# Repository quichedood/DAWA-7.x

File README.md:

# DAWA-7.x

Démo : https://youtu.be/l66AxoFr9uk

DAWA est un système de chronométrage et d'acquisition de données pour votre moto.
Il enregistre les données 10 fois par seconde dans un fichier CSV.

Specs/fonctionnalités :
- Ecran TFT tactile 4,3" couleur (resistif)
- Carte micro SD
- Antenne GPS externe
- Alimentation externe via batterie 12v
- Indicateur 8 leds paramétrable
- Position GPS (10Hz)
- Chronométrage circuit
- 2 entrées numériques (binaire)
- 2 entrées numériques (signal carré, fréquence)
- 8 entrées analogiques
- 6 capteurs de température infrarouge
- Module OBD (prise diagnostique)

Exemple de mesures :
- Vitesse (GPS ou basé sur une entrée numérique)
- Rapport de vitesse engagé (basé sur une entrée analogique)
- Régime moteur (basé sur une entrée numérique)
- Capteur de pression de frein (basé sur une entrée analogique)

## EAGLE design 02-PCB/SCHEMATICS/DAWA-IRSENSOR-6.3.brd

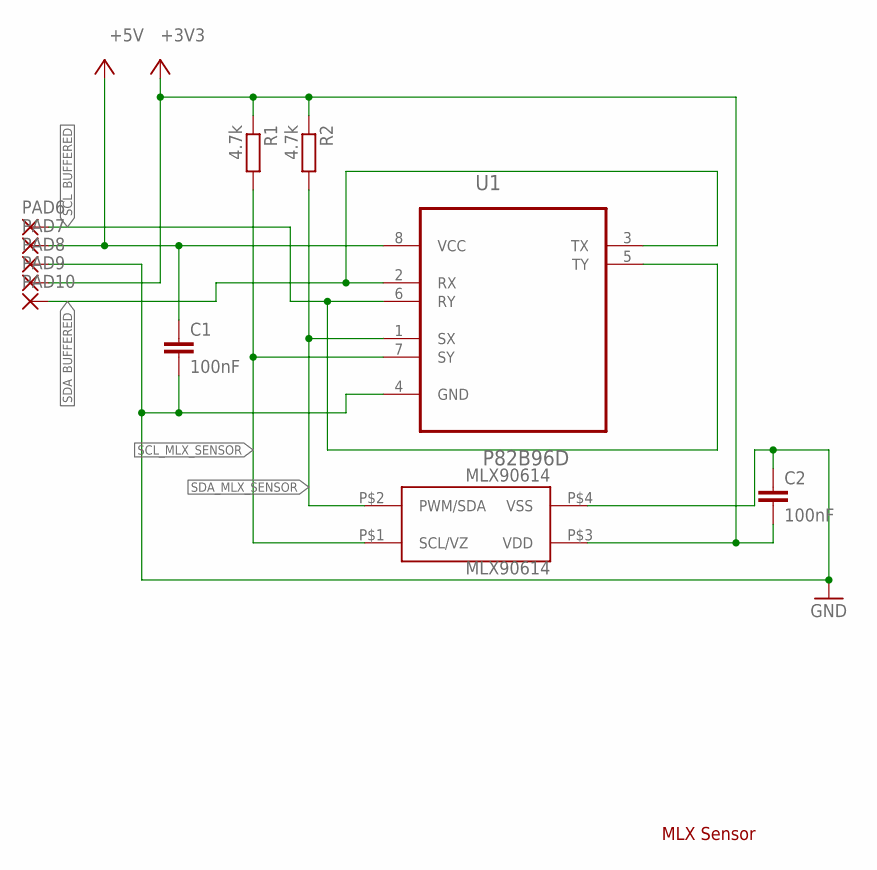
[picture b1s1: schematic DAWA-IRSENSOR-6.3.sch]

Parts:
C1, C2: 100nF; C0603
MLX90614: MLX90614; TO-39
PAD6, PAD7, PAD8, PAD9, PAD10: WIREPAD1,6/0,9; 1,6/0,9
R1, R2: 4.7k; R0603
U1: P82B96D; SOIC127P600X175-8N

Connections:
+3V3: C2.2, MLX90614.P$3 (VDD), PAD9.1, R1.1, R2.1
+5V: C1.1, PAD7.1, U1.8 (VCC)
GND: C1.2, C2.1, MLX90614.P$4 (VSS), PAD8.1, U1.4 (GND)
SCL_BUFFERED: PAD6.1, U1.5 (TY), U1.6 (RY)
SCL_MLX_SENSOR: MLX90614.P$1 (SCL/VZ), R1.2, U1.7 (SY)
SDA_BUFFERED: PAD10.1, U1.2 (RX), U1.3 (TX)
SDA_MLX_SENSOR: MLX90614.P$2 (PWM/SDA), R2.2, U1.1 (SX)

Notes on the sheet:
MLX Sensor

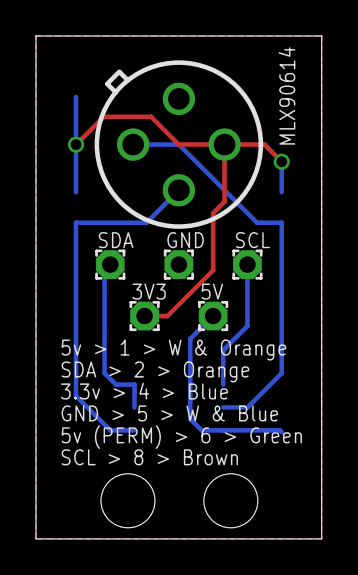
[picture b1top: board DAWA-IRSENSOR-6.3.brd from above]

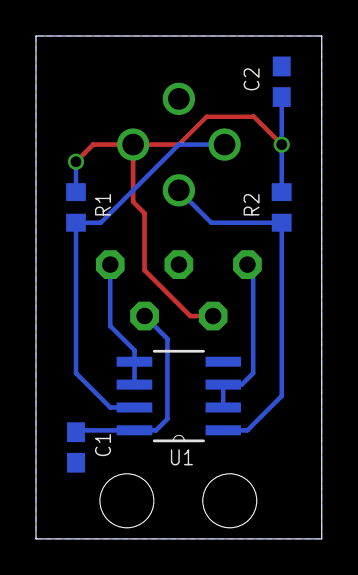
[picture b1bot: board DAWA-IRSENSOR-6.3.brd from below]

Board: 2 copper layers, 15.9 x 27.9 mm, 11 parts (5 on the bottom side), 7 nets.

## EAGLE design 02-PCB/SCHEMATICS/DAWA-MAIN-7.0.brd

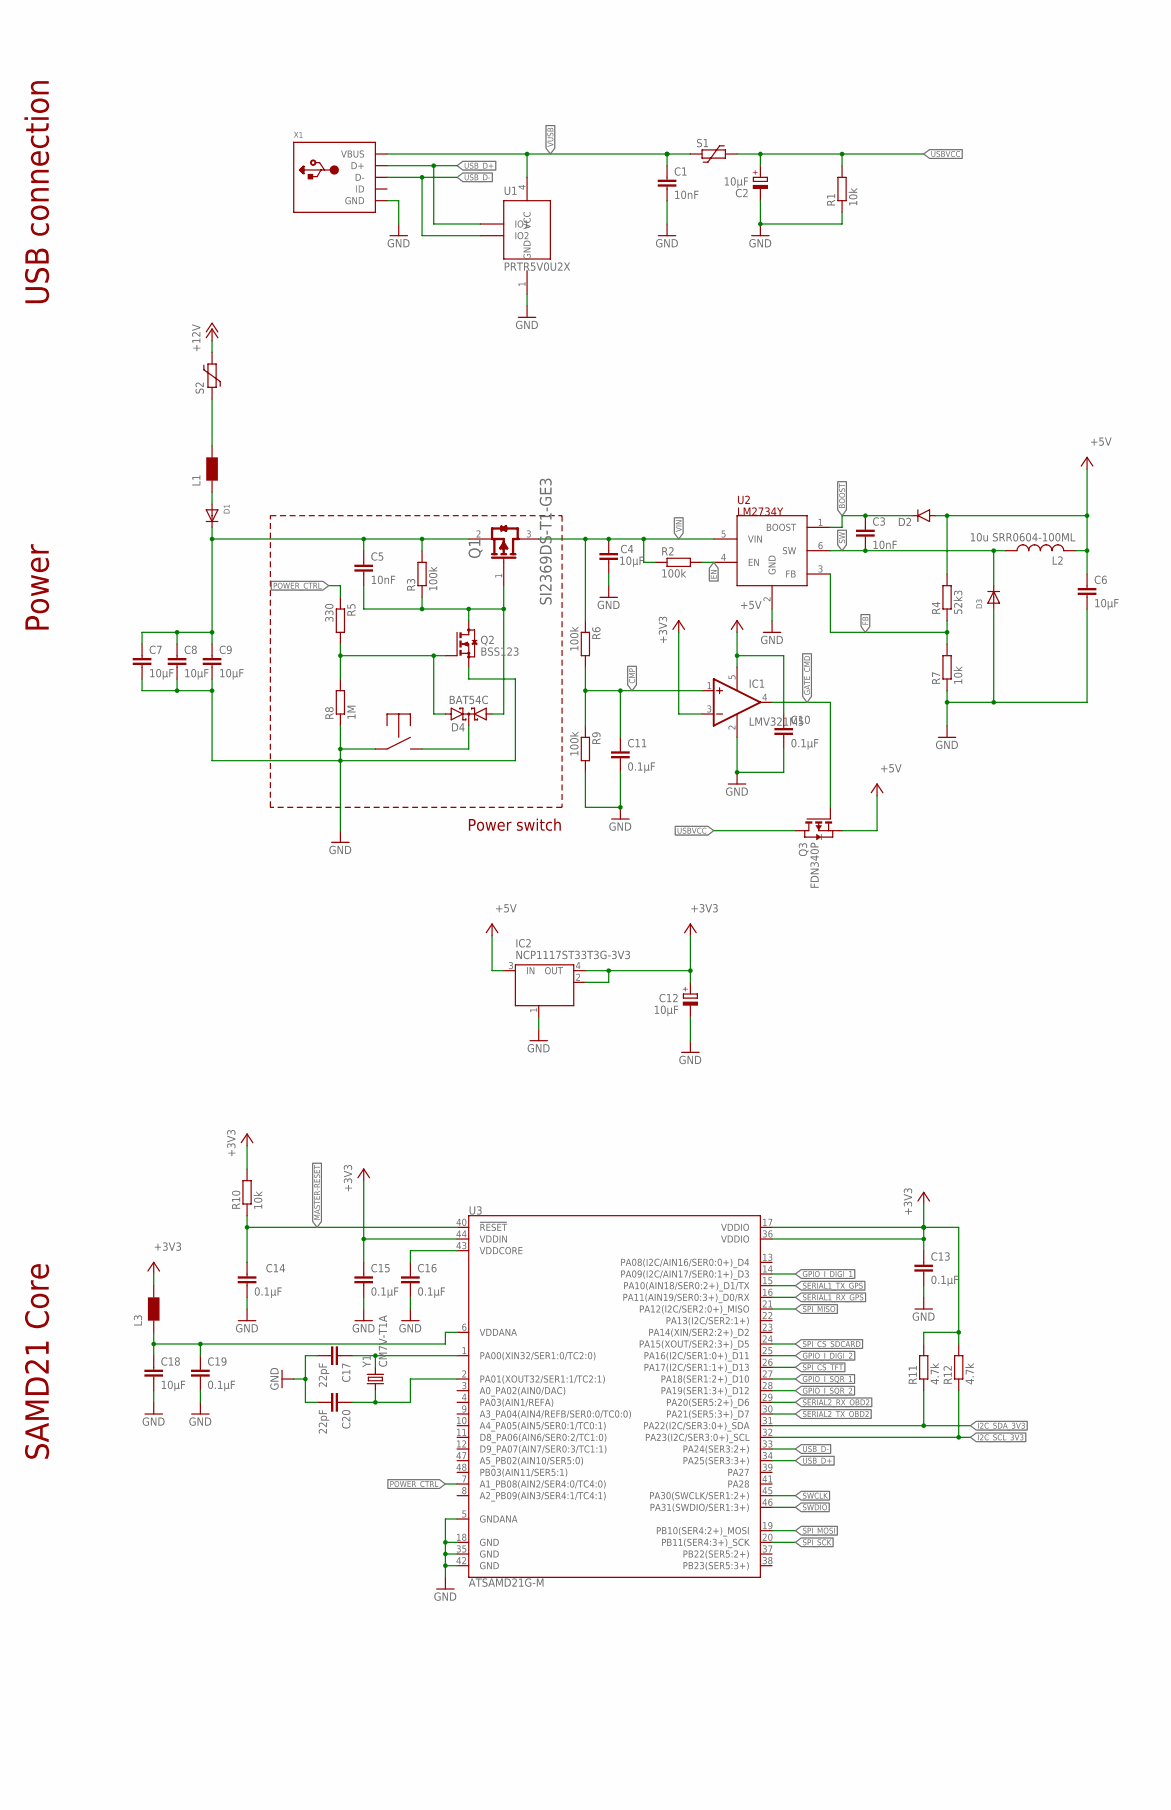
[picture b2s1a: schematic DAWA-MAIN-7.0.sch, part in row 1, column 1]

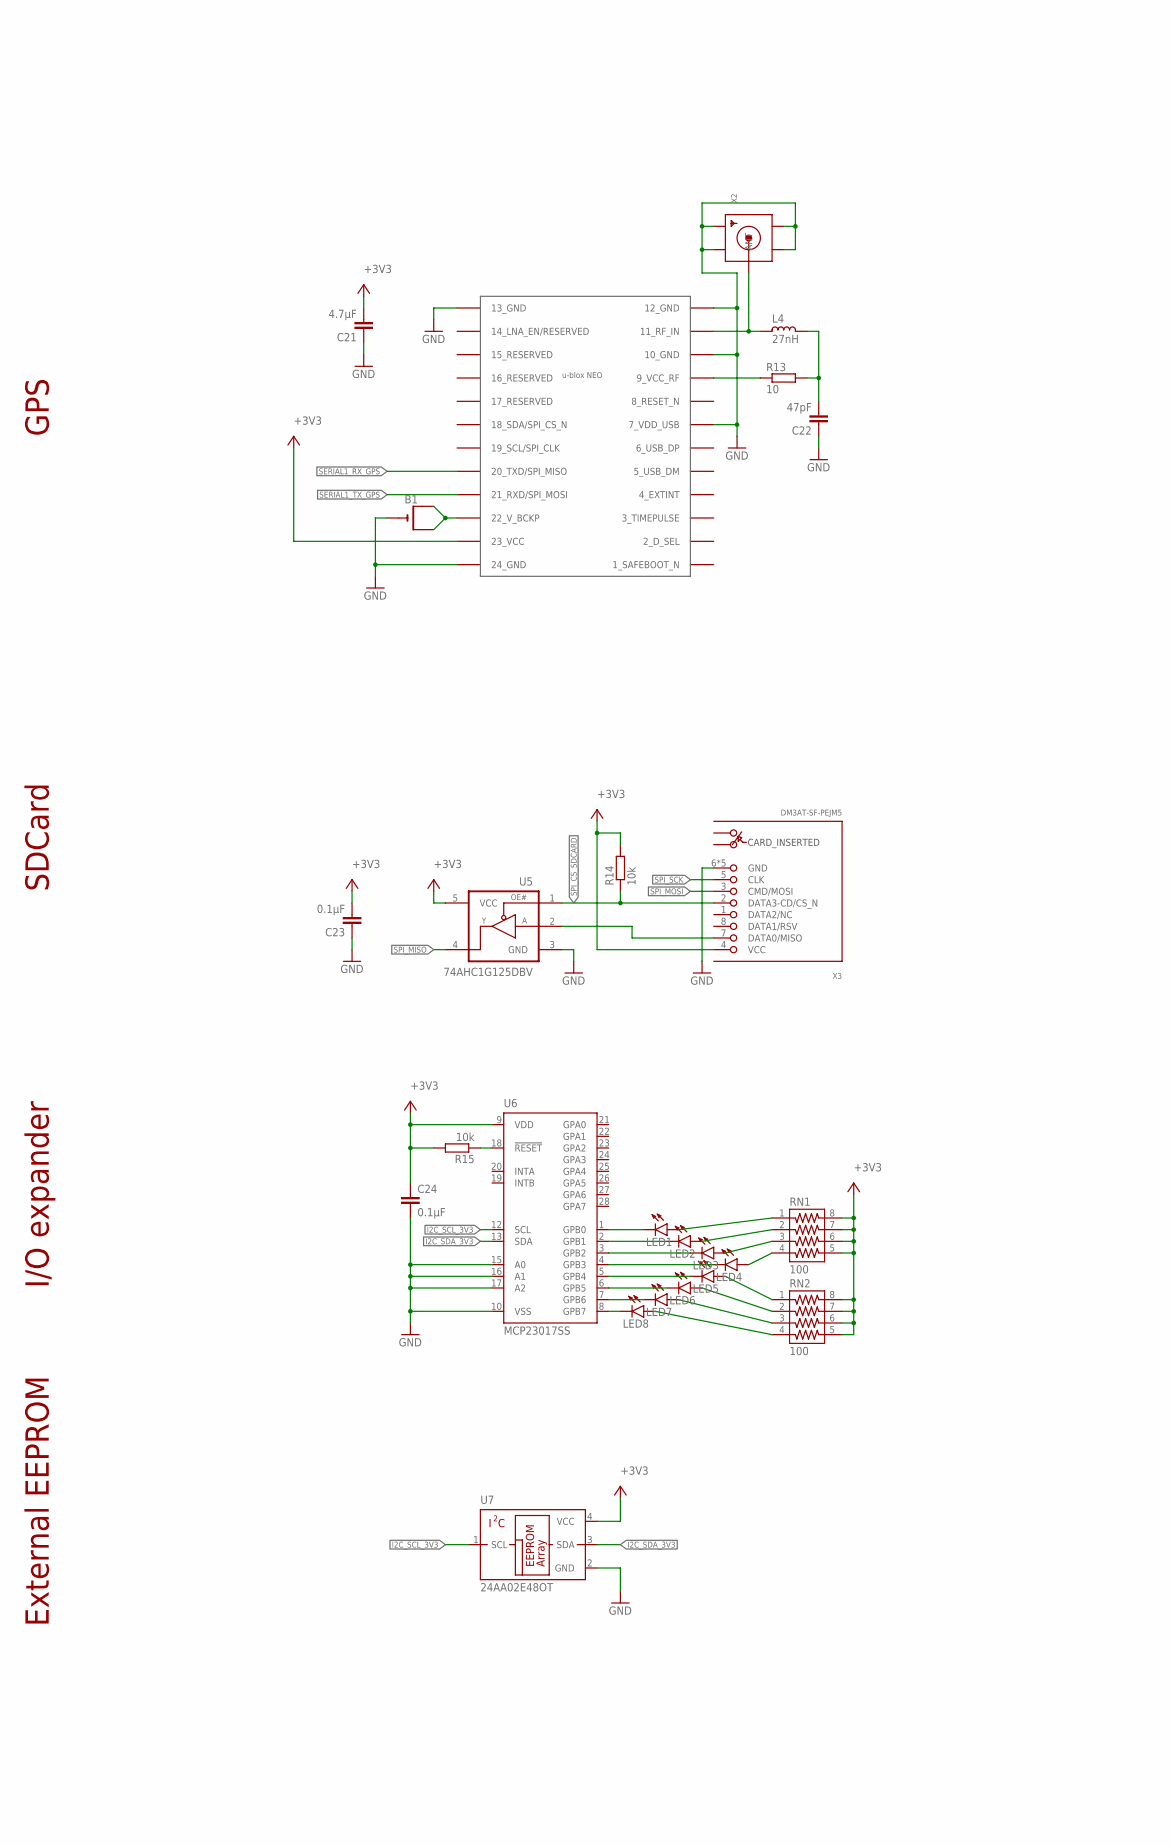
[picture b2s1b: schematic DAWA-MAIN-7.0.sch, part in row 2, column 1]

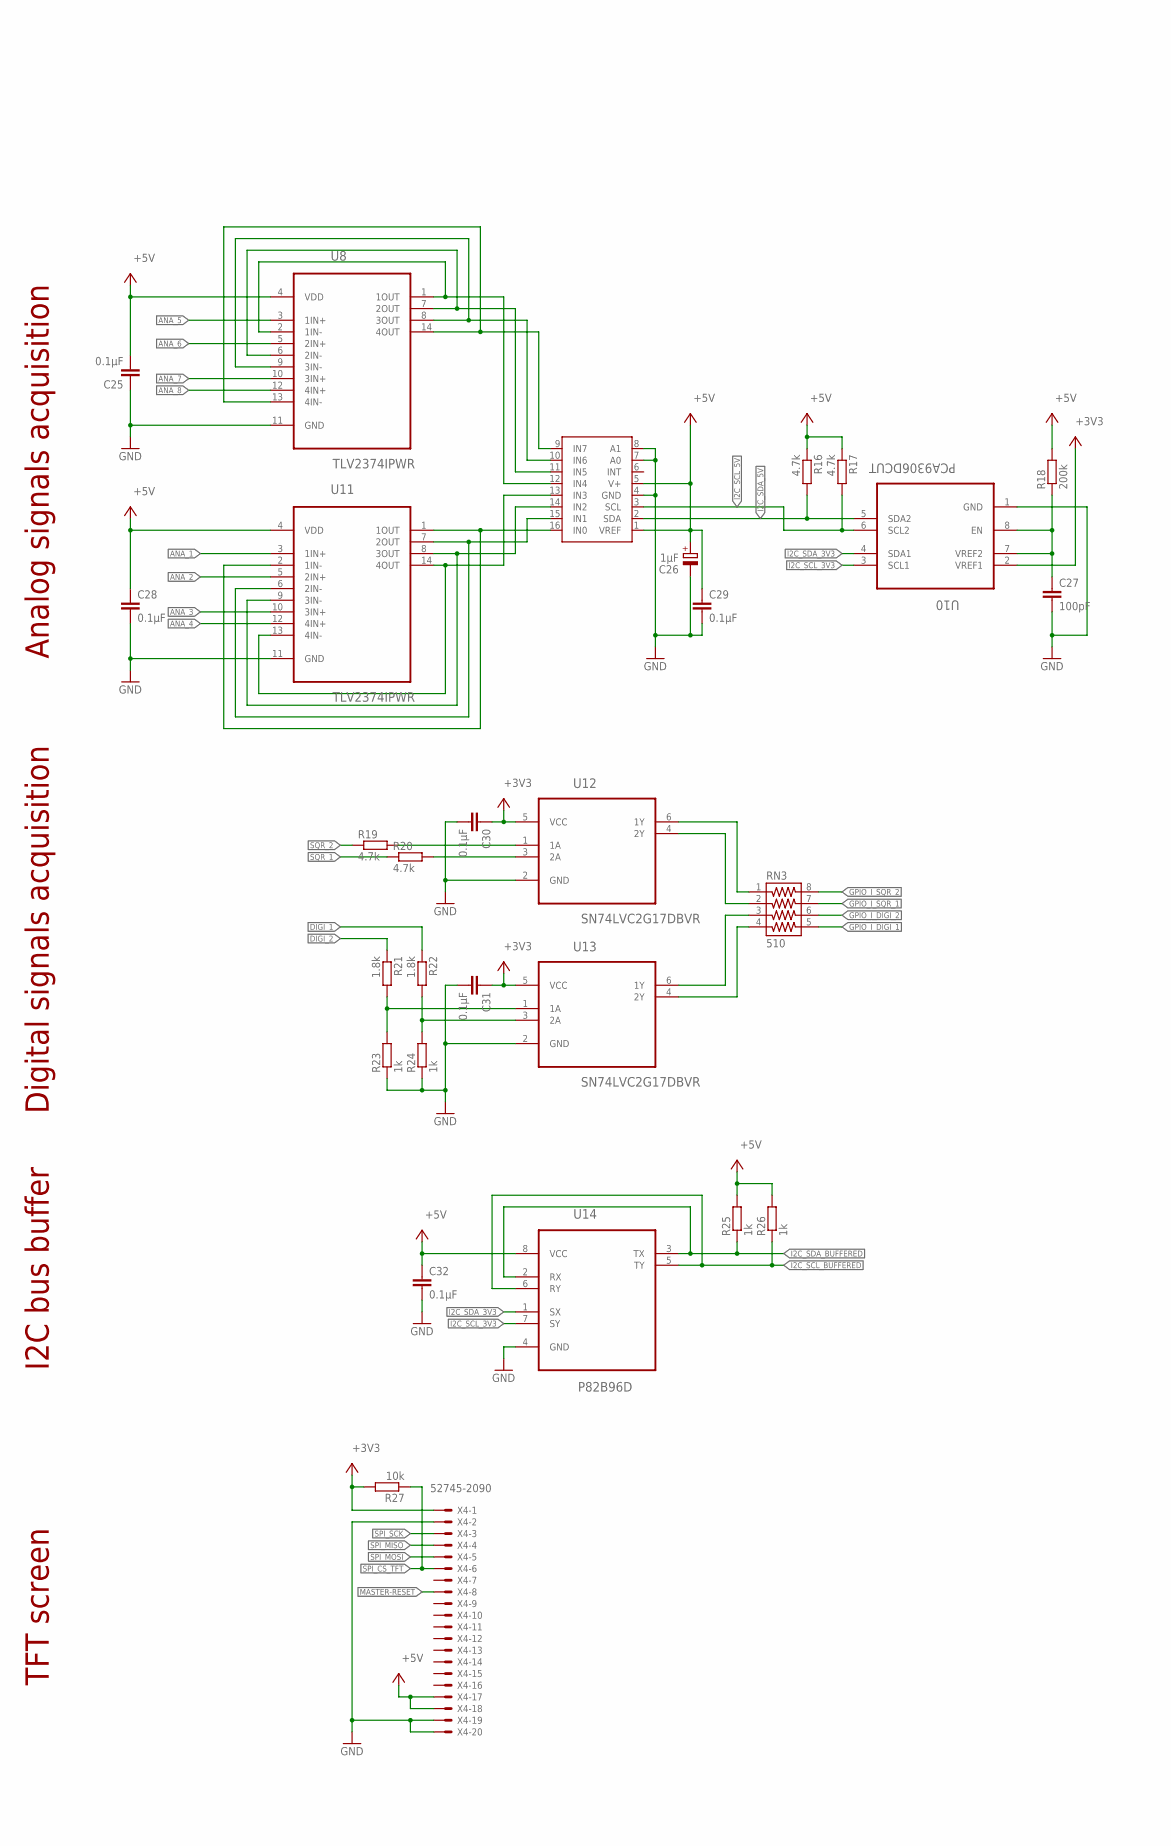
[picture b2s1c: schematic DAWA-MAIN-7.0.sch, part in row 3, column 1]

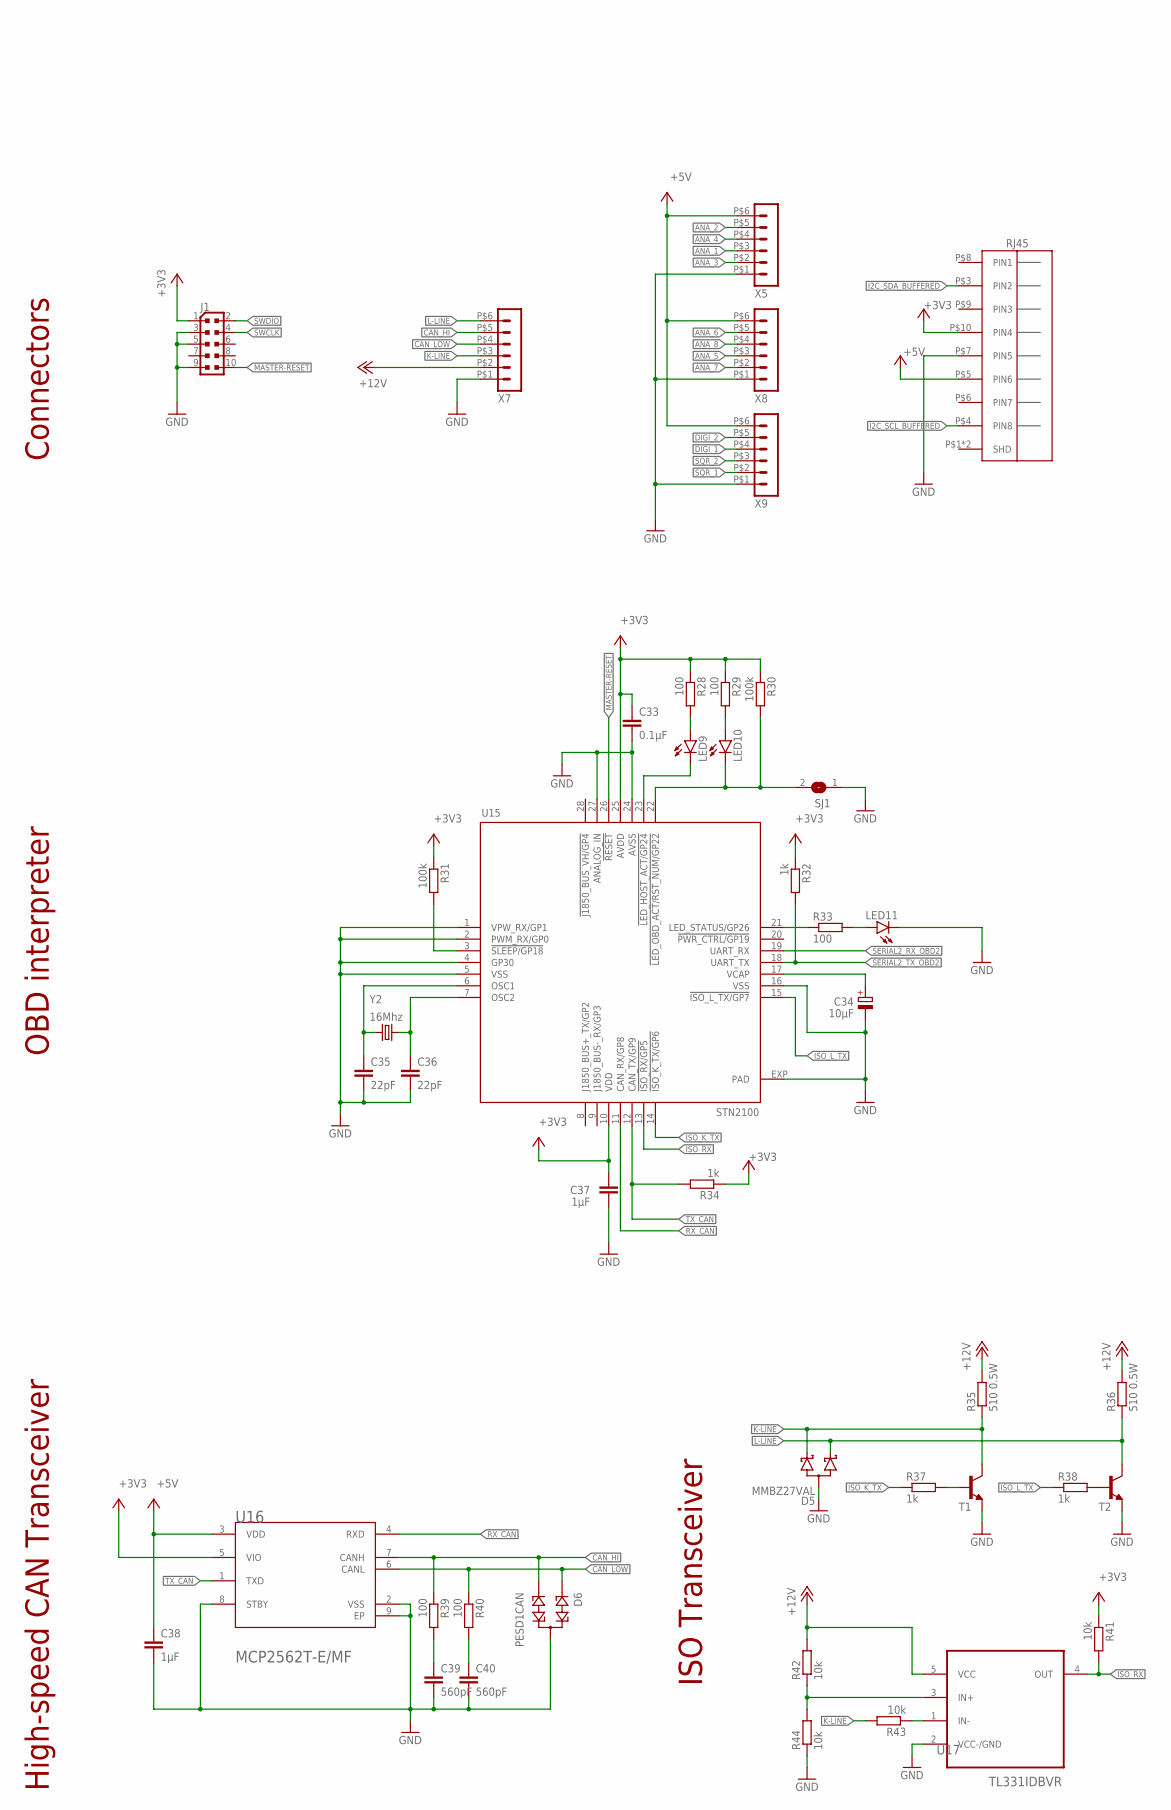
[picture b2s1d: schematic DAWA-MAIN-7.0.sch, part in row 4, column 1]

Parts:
B1: CR1220SMT; CR1220-SMD
C1, C3, C5: 10nF; C0603
C2, C12, C34: 10µF; SMC_B
C4, C6, C7, C8, C9, C18: 10µF; C0805
C10, C11, C13, C14, C15, C16, C19, C23, C24, C25, C28, C29, C30, C31, C32, C33: 0.1µF; C0603
C17, C20, C35, C36: 22pF; C0603
C21: 4.7µF; C0603
C22: 47pF; C0603
C26: 1µF; SMC_B
C27: 100pF; C0603
C37, C38: 1µF; C0603
C39, C40: 560pF; C0603
D1, D3: MBR120_SOD-123FL; SOD-123FL
D2: CD1206-S01575MINIMELF; MINIMELF
D4: BAT54C; SOT23
D5: MMBZ27VAL; SOT23
D6: PESD1CAN; SOT23
IC1: LMV321M5; SOT23-5
IC2: NCP1117ST33T3G-3V3; SOT223
J1: PINHD-2X5PASSO127; ARDUINO_WIFI_SHIELD_V018_TG_PINHEAD_2X05_127
L1, L3: MH2029-300Y_0805; WUERTH-ELEKTRONIK_0805
L2: 10u SRR0604-100ML; SRR0604
L4: 27nH; RC-MASTER-SMD_L0603
LED1, LED2, LED3, LED4, LED5, LED6, LED7, LED8, LED9, LED10, LED11: LEDCHIPLED_0603; CHIPLED_0603
Q1: SI2369DS-T1-GE3VISHAY_SI2369DS-T1-GE3_0_0; VISHAY_SI2369DS-T1-GE3_0
Q2: BSS123; SOT23
Q3: FDN340P; SOT-23
R1, R7, R10, R14, R15, R27, R41, R42, R43, R44: 10k; R0603
R2, R3, R6, R9, R30, R31: 100k; R0603
R4: 52k3; R0603
R5: 330; R0603
R8: 1M; R0603
R11, R12, R16, R17, R19, R20: 4.7k; R0603
R13: 10; R0603
R18: 200k; R0603
R21, R22: 1.8k; R0603
R23, R24, R25, R26, R32, R34, R37, R38: 1k; R0603
R28, R29, R33, R39, R40: 100; R0603
R35, R36: 510 0.5W; R0603
RN1, RN2: 100; 742-8NS
RN3: 510; 742-8NS
S1: MF-NSMF050-1206; MF-1206
S2: MF-MSMF050-1812; MF-1812
S3: SKPMAPE10
SJ1: SJ
T1, T2: MMBT2222ALT1-NPN-SOT23-BEC; SOT23-BEC
U1: PRTR5V0U2X; SOT-143B
U2: LM2734Y; SOT23-6
U3: ATSAMD21G-M; QFN-48
U4: NEO-M8
U5: 74AHC1G125DBV; SOT23-5
U6: MCP23017SS; SSOP28
U7: 24AA02E48OT; SOT23-5
U8, U11: TLV2374IPWR; SOP65P640X120-14N
U9: ADC128D818; ADC12_SD
U10: PCA9306DCUT; SOP50P310X90-8N
U12, U13: SN74LVC2G17DBVR; SOT95P280X145-6N
U14: P82B96D; SOIC127P600X175-8N
U15: STN2100; QFN-28-S
U16: MCP2562T-E-MFMICROCHIP_MCP2562T-E-MF_0_2; MICROCHIP_MCP2562T-E-MF_2
U17: TL331IDBVR; SOT95P280X145-5N
X1: USB; USB-MINIB-DAWA
X2: SMACONNECTOR_EDGE; SMA_EDGELAUNCH
X3: DM3AT-SF-PEJM5
X4: 52745-2090
X5, X7, X8, X9: HEADER_POS6_43045-0600; 43045-0600
X6: RJ45
Y1: CM7V-T1A; KANFLO_OSCILLATOR_SMD
Y2: 16Mhz; 3.2X2.5_KX-7

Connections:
+3V3: C12.+, C13.1, C15.1, C21.2, C23.2, C24.1, C30.1, C31.1, C33.1, C37.1, IC1.3 (-IN), IC2.2 (OUT), IC2.4 (OUT), J1.1, L3.2, R10.2, R11.2, R12.2, R14.2, R15.2, R27.2, R28.1, R29.1, R30.1, R31.1, R32.1, R34.1, R41.1, RN1.5, RN1.6, RN1.7, RN1.8, RN2.5, RN2.6, RN2.7, RN2.8, U3.17 (VDDIO), U3.36 (VDDIO), U3.44 (VDDIN), U4.23 (23_VCC), U5.5 (VCC), U6.9 (VDD), U7.4 (VCC), U10.2 (VREF1), U12.5 (VCC), U13.5 (VCC), U15.10 (VDD), U15.25 (AVDD), U16.5 (VIO), X3.4 (VCC), X4.1, X6.P$10 (PIN4)
+5V: C6.1, C10.1, C25.2, C26.+, C28.1, C29.1, C32.1, C38.1, D2.A, IC1.5 (V+), IC2.3 (IN), L2.P$2 (2), Q3.2 (S), R4.2, R16.1, R17.1, R18.2, R25.2, R26.2, U8.4 (VDD), U9.1 (VREF), U9.5 (V+), U11.4 (VDD), U14.8 (VCC), U16.3 (VDD), X4.17, X4.18, X5.P$6 (6), X6.P$5 (PIN6), X8.P$6 (6), X9.P$6 (6)
+12V: R35.2, R36.2, R42.2, S2.1, U17.5 (VCC), X7.P$2 (2)
ANA_1: U11.3 (1IN+), X5.P$3 (3)
ANA_2: U11.5 (2IN+), X5.P$5 (5)
ANA_3: U11.10 (3IN+), X5.P$2 (2)
ANA_4: U11.12 (4IN+), X5.P$4 (4)
ANA_5: U8.3 (1IN+), X8.P$3 (3)
ANA_6: U8.5 (2IN+), X8.P$5 (5)
ANA_7: U8.10 (3IN+), X8.P$2 (2)
ANA_8: U8.12 (4IN+), X8.P$4 (4)
BOOST: C3.1, D2.C, U2.1 (BOOST)
CAN_HI: D6.2, R39.1, U16.7 (CANH), X7.P$5 (5)
CAN_LOW: D6.1, R40.1, U16.6 (CANL), X7.P$4 (4)
CMP: C11.1, IC1.1 (+IN), R6.2, R9.1
DIGI_1: R22.1, X9.P$4 (4)
DIGI_2: R21.1, X9.P$5 (5)
EN: R2.2, U2.4 (EN)
FB: R4.1, R7.2, U2.3 (FB)
GATE_CMD: IC1.4 (OUT), Q3.3 (G)
GND: B1.-, C1.2, C2.-, C4.2, C6.2, C7.2, C8.2, C9.2, C10.2, C11.2, C12.-, C13.2, C14.2, C15.2, C16.2, C17.2, C18.2, C19.2, C20.2, C21.1, C22.1, C23.1, C24.2, C25.1, C26.-, C27.2, C28.2, C29.2, C30.2, C31.2, C32.2, C33.2, C34.-, C35.2, C36.2, C37.2, C38.2, C39.2, C40.2, D3.A, D5.3 (A), D6.3, IC1.2 (V-), IC2.1 (GND/ADJ), J1.3, J1.5, J1.9, LED11.C, Q2.2 (S), R1.1, R7.1, R8.1, R9.2, R23.1, R24.1, R44.1, S3.P$1, SJ1.1, T1.E, T2.E, U1.1 (GND), U2.2 (GND), U3.5 (GNDANA), U3.18 (GND), U3.35 (GND), U3.42 (GND), U4.7 (7_VDD_USB), U4.10 (10_GND), U4.12 (12_GND), U4.13 (13_GND), U4.24 (24_GND), U5.3 (GND), U6.10 (VSS), U6.15 (A0), U6.16 (A1), U6.17 (A2), U7.2 (GND), U8.11 (GND), U9.4 (GND), U9.7 (A0), U9.8 (A1), U10.1 (GND), U11.11 (GND), U12.2 (GND), U13.2 (GND), U14.4 (GND), U15.1 (VPW_RX/GP1), U15.2 (PWM_RX/GP0), U15.4 (GP30), U15.5 (VSS), U15.16 (VSS), U15.24 (AVSS), U15.27 (ANALOG_IN), U15.EXP (PAD), U16.2 (VSS), U16.8 (STBY), U16.9 (EP), U17.2 (VCC-/GND), X1.GND, X1.GND1 (GND), X1.GND2 (GND), X2.GND@1 (GND4), X2.GND@2 (GND3), X2.GND@3 (GND2), X2.GND@4 (GND1), X3.6 (GND), X3.MOUNT0 (GND), X3.MOUNT1 (GND), X3.MOUNT2 (GND), X3.MOUNT3 (GND), X4.2, X4.19, X4.20, X5.P$1 (1), X6.P$7 (PIN5), X7.P$1 (1), X8.P$1 (1), X9.P$1 (1)
GPIO_I_DIGI_1: RN3.5, U3.14 (PA09(I2C/AIN17/SER0:1+)_D3)
GPIO_I_DIGI_2: RN3.6, U3.25 (PA16(I2C/SER1:0+)_D11)
GPIO_I_SQR_1: RN3.7, U3.27 (PA18(SER1:2+)_D10)
GPIO_I_SQR_2: RN3.8, U3.28 (PA19(SER1:3+)_D12)
I2C_SCL_3V3: R12.1, U3.32 (PA23(I2C/SER3:0+)_SCL), U6.12 (SCL), U7.1 (SCL), U10.3 (SCL1), U14.7 (SY)
I2C_SCL_5V: R17.2, U9.3 (SCL), U10.6 (SCL2)
I2C_SCL_BUFFERED: R26.1, U14.5 (TY), U14.6 (RY), X6.P$4 (PIN8)
I2C_SDA_3V3: R11.1, U3.31 (PA22(I2C/SER3:0+)_SDA), U6.13 (SDA), U7.3 (SDA), U10.4 (SDA1), U14.1 (SX)
I2C_SDA_5V: R16.2, U9.2 (SDA), U10.5 (SDA2)
I2C_SDA_BUFFERED: R25.1, U14.2 (RX), U14.3 (TX), X6.P$3 (PIN2)
ISO_K_TX: R37.1, U15.14 (!ISO_K_TX/GP6)
ISO_L_TX: R38.1, U15.15 (!ISO_L_TX/GP7)
ISO_RX: R41.2, U15.13 (!ISO_RX/GP5), U17.4 (OUT)
K-LINE: D5.2 (C2), R35.1, R43.2, T1.C, X7.P$3 (3)
L-LINE: D5.1 (C1), R36.1, T2.C, X7.P$6 (6)
MASTER-RESET: C14.1, J1.10, R10.1, U3.40 (!RESET!), U15.26 (!RESET), X4.8
unnamed: C16.1, U3.43 (VDDCORE)
unnamed: C17.1, U3.1 (PA00(XIN32/SER1:0/TC2:0)), Y1.2
unnamed: C20.1, U3.2 (PA01(XOUT32/SER1:1/TC2:1)), Y1.1
unnamed: LED1.C, U6.1 (GPB0)
unnamed: B1.+$1 (+), B1.+$2 (+1), U4.22 (22_V_BCKP)
unnamed: LED2.C, U6.2 (GPB1)
unnamed: C5.1, C7.1, C8.1, C9.1, D1.C, Q1.2 (S), R3.2
unnamed: LED1.A, RN1.1
unnamed: D1.A, L1.1
unnamed: C22.2, L4.1, R13.2
unnamed: LED2.A, RN1.2
unnamed: U5.2 (A), X3.7 (DATA0/MISO)
unnamed: LED5.C, U6.5 (GPB4)
unnamed: C27.1, R18.1, U10.7 (VREF2), U10.8 (EN)
unnamed: LED6.C, U6.6 (GPB5)
unnamed: LED7.C, U6.7 (GPB6)
unnamed: LED8.C, U6.8 (GPB7)
unnamed: R13.1, U4.9 (9_VCC_RF)
unnamed: L4.2, U4.11 (11_RF_IN), X2.P (ANT)
unnamed: LED3.A, RN1.3
unnamed: LED3.C, U6.3 (GPB2)
unnamed: LED4.C, U6.4 (GPB3)
unnamed: LED4.A, RN1.4
unnamed: LED5.A, RN2.1
unnamed: LED6.A, RN2.2
unnamed: U9.16 (IN0), U11.1 (1OUT), U11.2 (1IN-)
unnamed: U9.15 (IN1), U11.6 (2IN-), U11.7 (2OUT)
unnamed: LED7.A, RN2.3
unnamed: LED8.A, RN2.4
unnamed: U9.14 (IN2), U11.8 (3OUT), U11.9 (3IN-)
unnamed: LED10.C, R30.2, SJ1.2, U15.22 (!LED_OBD_ACT/RST_NUM/GP22)
unnamed: R37.2, T1.B
unnamed: R15.1, U6.18 (!RESET)
unnamed: U9.13 (IN3), U11.13 (4IN-), U11.14 (4OUT)
unnamed: RN3.1, U12.6 (1Y)
unnamed: L1.2, S2.2
unnamed: U8.8 (3OUT), U8.9 (3IN-), U9.10 (IN6)
unnamed: U8.6 (2IN-), U8.7 (2OUT), U9.11 (IN5)
unnamed: U8.1 (1OUT), U8.2 (1IN-), U9.12 (IN4)
unnamed: R19.2, U12.1 (1A)
unnamed: R20.2, U12.3 (2A)
unnamed: R22.2, R24.2, U13.3 (2A)
unnamed: R21.2, R23.2, U13.1 (1A)
unnamed: RN3.3, U13.6 (1Y)
unnamed: RN3.4, U13.4 (2Y)
unnamed: C5.2, D4.1 (A1), Q1.1 (G), Q2.3 (D), R3.1
unnamed: D4.3 (CC), S3.P$2
unnamed: RN3.2, U12.4 (2Y)
unnamed: D4.2 (A2), Q2.1 (G), R5.2, R8.2
unnamed: U8.13 (4IN-), U8.14 (4OUT), U9.9 (IN7)
unnamed: R38.2, T2.B
unnamed: R42.1, R44.2, U17.3 (IN+)
unnamed: R43.1, U17.1 (IN-)
unnamed: R31.2, U15.3 (!SLEEP/GP18)
unnamed: C35.1, U15.6 (OSC1), Y2.1
unnamed: C36.1, U15.7 (OSC2), Y2.3 (2)
unnamed: LED9.A, R28.2
unnamed: C34.+, U15.17 (VCAP)
unnamed: R33.1, U15.21 (LED_STATUS/GP26)
unnamed: LED11.A, R33.2
unnamed: LED10.A, R29.2
unnamed: LED9.C, U15.23 (!LED_HOST_ACT/GP24)
unnamed: C39.1, R39.2
unnamed: C40.1, R40.2
POWER_CTRL: R5.1, U3.7 (A1_PB08(AIN2/SER4:0/TC4:0))
RX_CAN: U15.11 (CAN_RX/GP8), U16.4 (RXD)
SERIAL1_RX_GPS: U3.16 (PA11(AIN19/SER0:3+)_D0/RX), U4.20 (20_TXD/SPI_MISO)
SERIAL1_TX_GPS: U3.15 (PA10(AIN18/SER0:2+)_D1/TX), U4.21 (21_RXD/SPI_MOSI)
SERIAL2_RX_OBD2: U3.29 (PA20(SER5:2+)_D6), U15.19 (UART_RX)
SERIAL2_TX_OBD2: R32.2, U3.30 (PA21(SER5:3+)_D7), U15.18 (UART_TX)
SPI_CS_SDCARD: R14.1, U3.24 (PA15(XOUT/SER2:3+)_D5), U5.1 (OE#), X3.2 (DATA3-CD/CS_N)
SPI_CS_TFT: R27.1, U3.26 (PA17(I2C/SER1:1+)_D13), X4.6
SPI_MISO: U3.21 (PA12(I2C/SER2:0+)_MISO), U5.4 (Y), X4.4
SPI_MOSI: U3.19 (PB10(SER4:2+)_MOSI), X3.3 (CMD/MOSI), X4.5
SPI_SCK: U3.20 (PB11(SER4:3+)_SCK), X3.5 (CLK), X4.3
SQR_1: R20.1, X9.P$2 (2)
SQR_2: R19.1, X9.P$3 (3)
SW: C3.2, D3.C, L2.P$1 (1), U2.6 (SW)
SWCLK: J1.4, U3.45 (PA30(SWCLK/SER1:2+))
SWDIO: J1.2, U3.46 (PA31(SWDIO/SER1:3+))
TX_CAN: R34.2, U15.12 (CAN_TX/GP9), U16.1 (TXD)
USBVCC: C2.+, Q3.1 (D), R1.2, S1.2
USB_D+: U1.2 (IO1), U3.34 (PA25(SER3:3+)), X1.D+
USB_D-: U1.3 (IO2), U3.33 (PA24(SER3:2+)), X1.D-
VDDANA: C18.1, C19.1, L3.1, U3.6 (VDDANA)
VIN: C4.1, Q1.3 (D), R2.1, R6.1, U2.5 (VIN)
VUSB: C1.1, S1.1, U1.4 (VCC), X1.VBUS

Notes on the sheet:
SAMD21 Core
Power
USB connection
GPS
SDCard
I/O expander
Analog signals acquisition
Digital signals acquisition
I2C bus buffer
External EEPROM
Connectors
OBD interpreter
High-speed CAN Transceiver
TFT screen
Power switch
ISO Transceiver

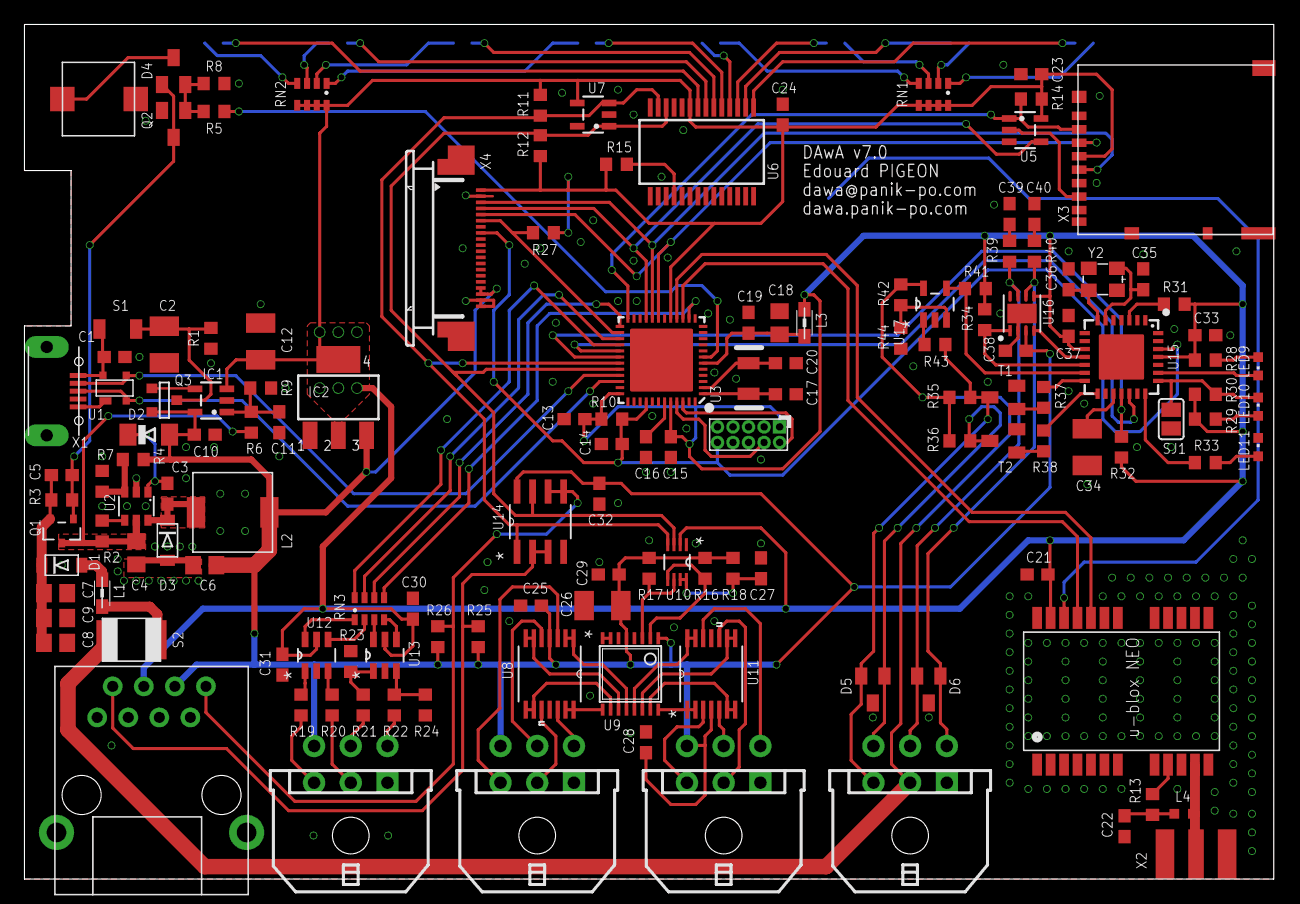
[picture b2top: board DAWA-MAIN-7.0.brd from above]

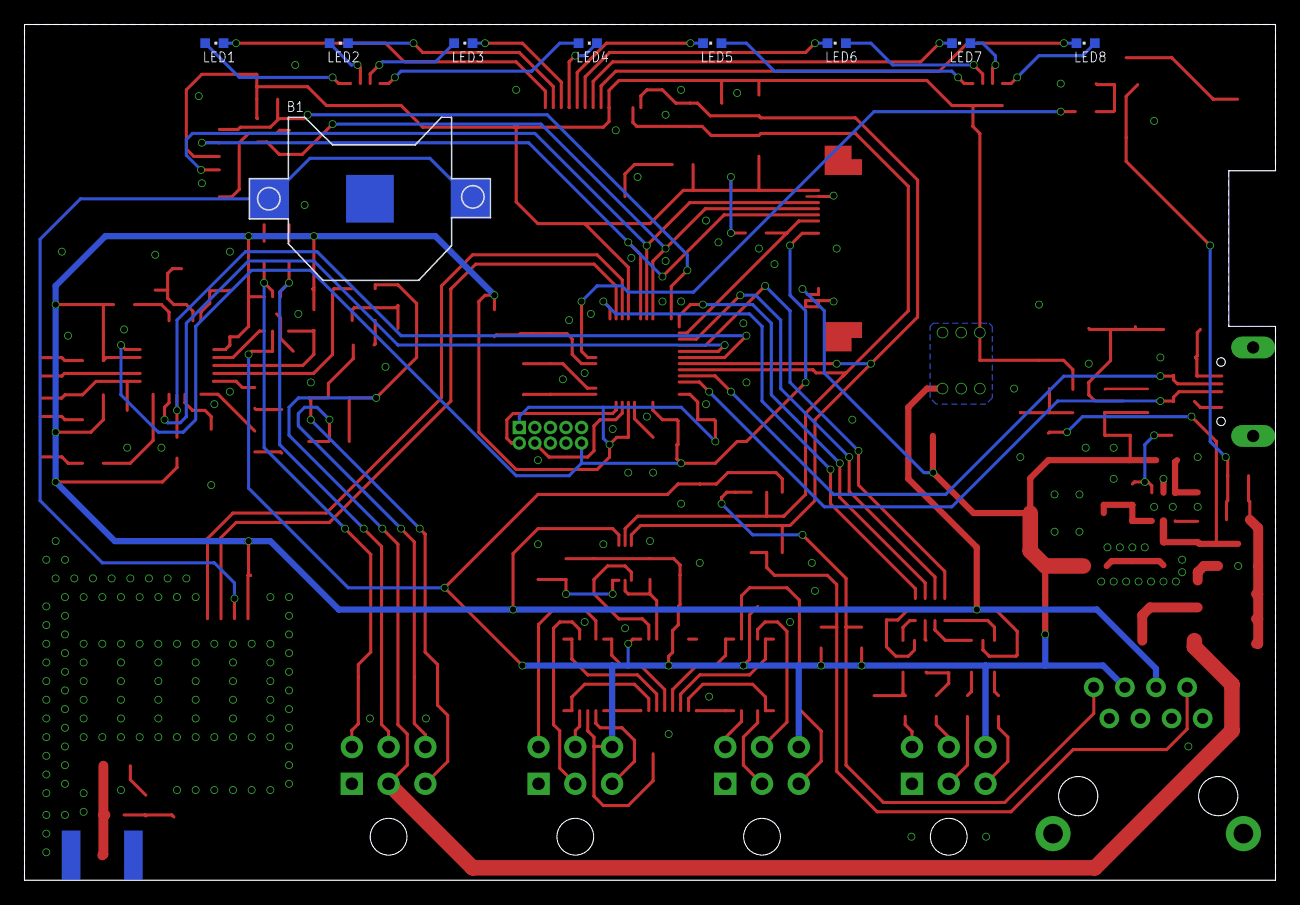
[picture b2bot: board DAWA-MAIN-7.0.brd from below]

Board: 2 copper layers, 102.1 x 69.8 mm, 149 parts (9 on the bottom side), 124 nets.

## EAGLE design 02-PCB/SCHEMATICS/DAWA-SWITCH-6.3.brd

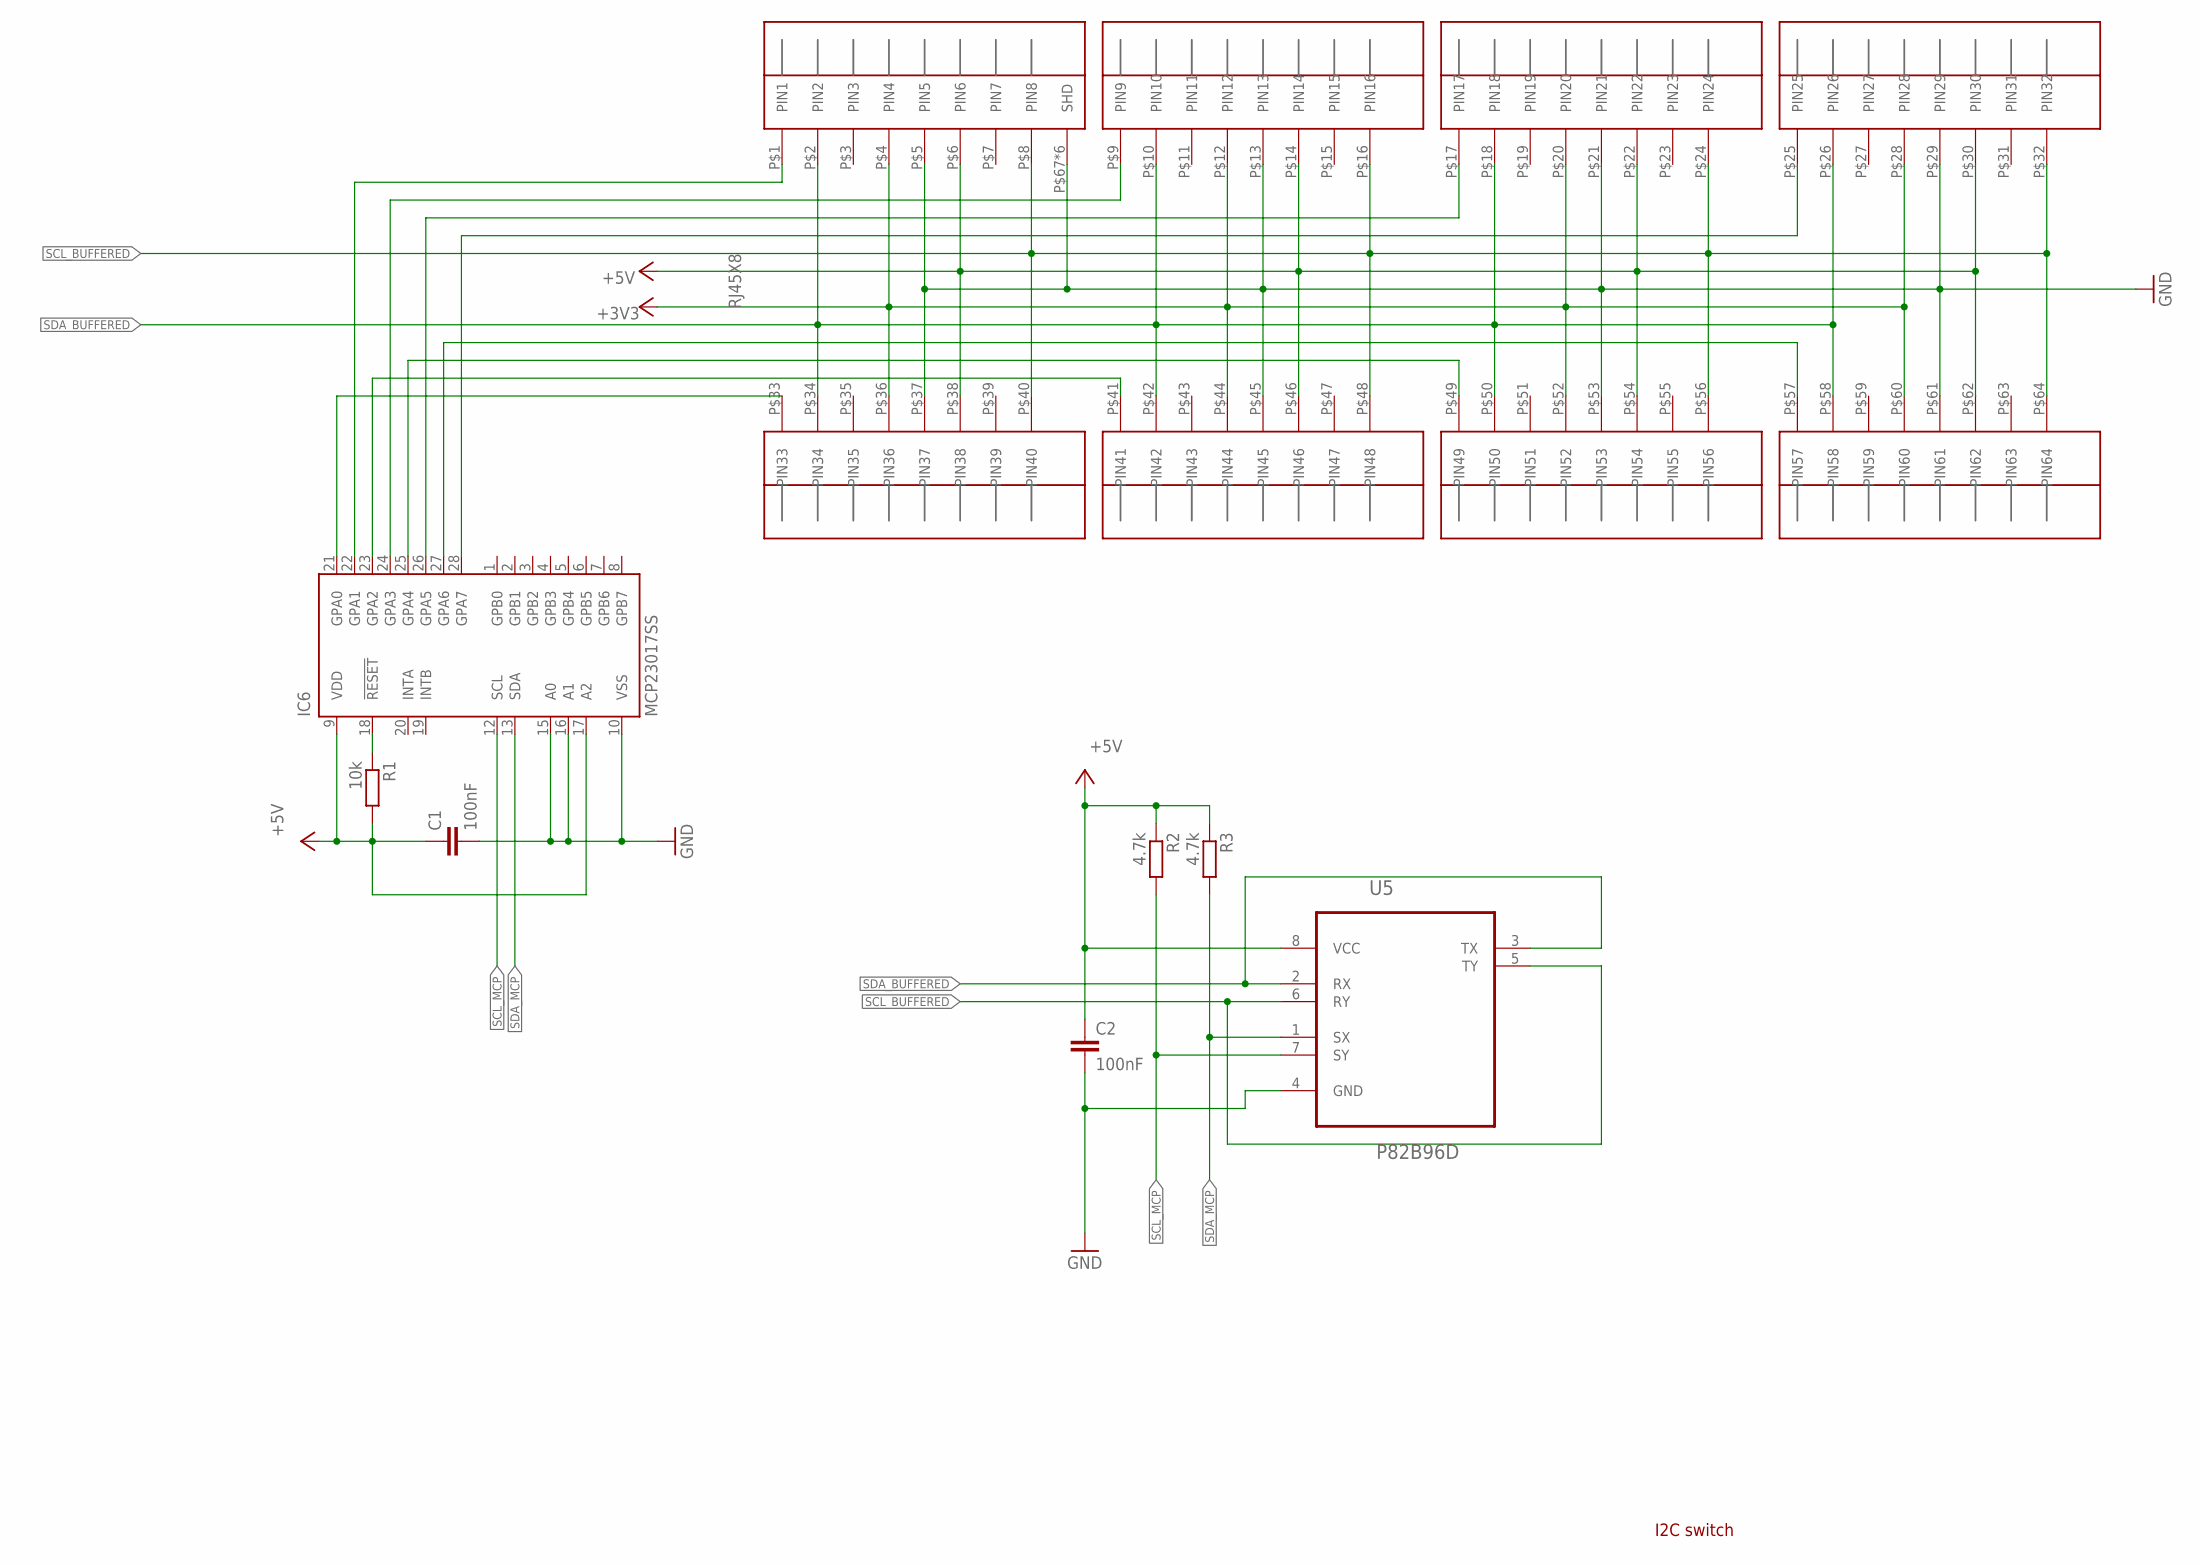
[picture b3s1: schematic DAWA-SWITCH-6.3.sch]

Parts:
C1, C2: 100nF; C0603
IC6: MCP23017SS; SSOP28
R1: 10k; R0603
R2, R3: 4.7k; R0603
U5: P82B96D; SOIC127P600X175-8N
U$18: RJ45X8

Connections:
+3V3: U$18.P$4 (PIN4), U$18.P$12 (PIN12), U$18.P$20 (PIN20), U$18.P$28 (PIN28), U$18.P$36 (PIN36), U$18.P$44 (PIN44), U$18.P$52 (PIN52), U$18.P$60 (PIN60)
+5V: C1.1, C2.1, IC6.9 (VDD), IC6.17 (A2), R1.2, R2.1, R3.1, U5.8 (VCC), U$18.P$6 (PIN6), U$18.P$14 (PIN14), U$18.P$22 (PIN22), U$18.P$30 (PIN30), U$18.P$38 (PIN38), U$18.P$46 (PIN46), U$18.P$54 (PIN54), U$18.P$62 (PIN62)
GND: C1.2, C2.2, IC6.10 (VSS), IC6.15 (A0), IC6.16 (A1), U5.4 (GND), U$18.P$5 (PIN5), U$18.P$13 (PIN13), U$18.P$21 (PIN21), U$18.P$29 (PIN29), U$18.P$37 (PIN37), U$18.P$45 (PIN45), U$18.P$53 (PIN53), U$18.P$61 (PIN61), U$18.P$67 (SHD), U$18.P$68 (SHD), U$18.P$69 (SHD), U$18.P$70 (SHD), U$18.P$71 (SHD), U$18.P$72 (SHD)
unnamed: IC6.28 (GPA7), U$18.P$25 (PIN25)
unnamed: IC6.26 (GPA5), U$18.P$17 (PIN17)
unnamed: IC6.24 (GPA3), U$18.P$9 (PIN9)
unnamed: IC6.22 (GPA1), U$18.P$1 (PIN1)
unnamed: IC6.21 (GPA0), U$18.P$33 (PIN33)
unnamed: IC6.23 (GPA2), U$18.P$41 (PIN41)
unnamed: IC6.25 (GPA4), U$18.P$49 (PIN49)
unnamed: IC6.27 (GPA6), U$18.P$57 (PIN57)
unnamed: IC6.18 (!RESET), R1.1
SCL_BUFFERED: U5.5 (TY), U5.6 (RY), U$18.P$8 (PIN8), U$18.P$16 (PIN16), U$18.P$24 (PIN24), U$18.P$32 (PIN32), U$18.P$40 (PIN40), U$18.P$48 (PIN48), U$18.P$56 (PIN56), U$18.P$64 (PIN64)
SCL_MCP: IC6.12 (SCL), R2.2, U5.7 (SY)
SDA_BUFFERED: U5.2 (RX), U5.3 (TX), U$18.P$2 (PIN2), U$18.P$10 (PIN10), U$18.P$18 (PIN18), U$18.P$26 (PIN26), U$18.P$34 (PIN34), U$18.P$42 (PIN42), U$18.P$50 (PIN50), U$18.P$58 (PIN58)
SDA_MCP: IC6.13 (SDA), R3.2, U5.1 (SX)

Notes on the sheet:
I2C switch

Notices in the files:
parts and their libraries:
SparkFun-Aesthetics: Licensing: CC v3.0 Share-Alike You are welcome to use this library for commercial purposes.
